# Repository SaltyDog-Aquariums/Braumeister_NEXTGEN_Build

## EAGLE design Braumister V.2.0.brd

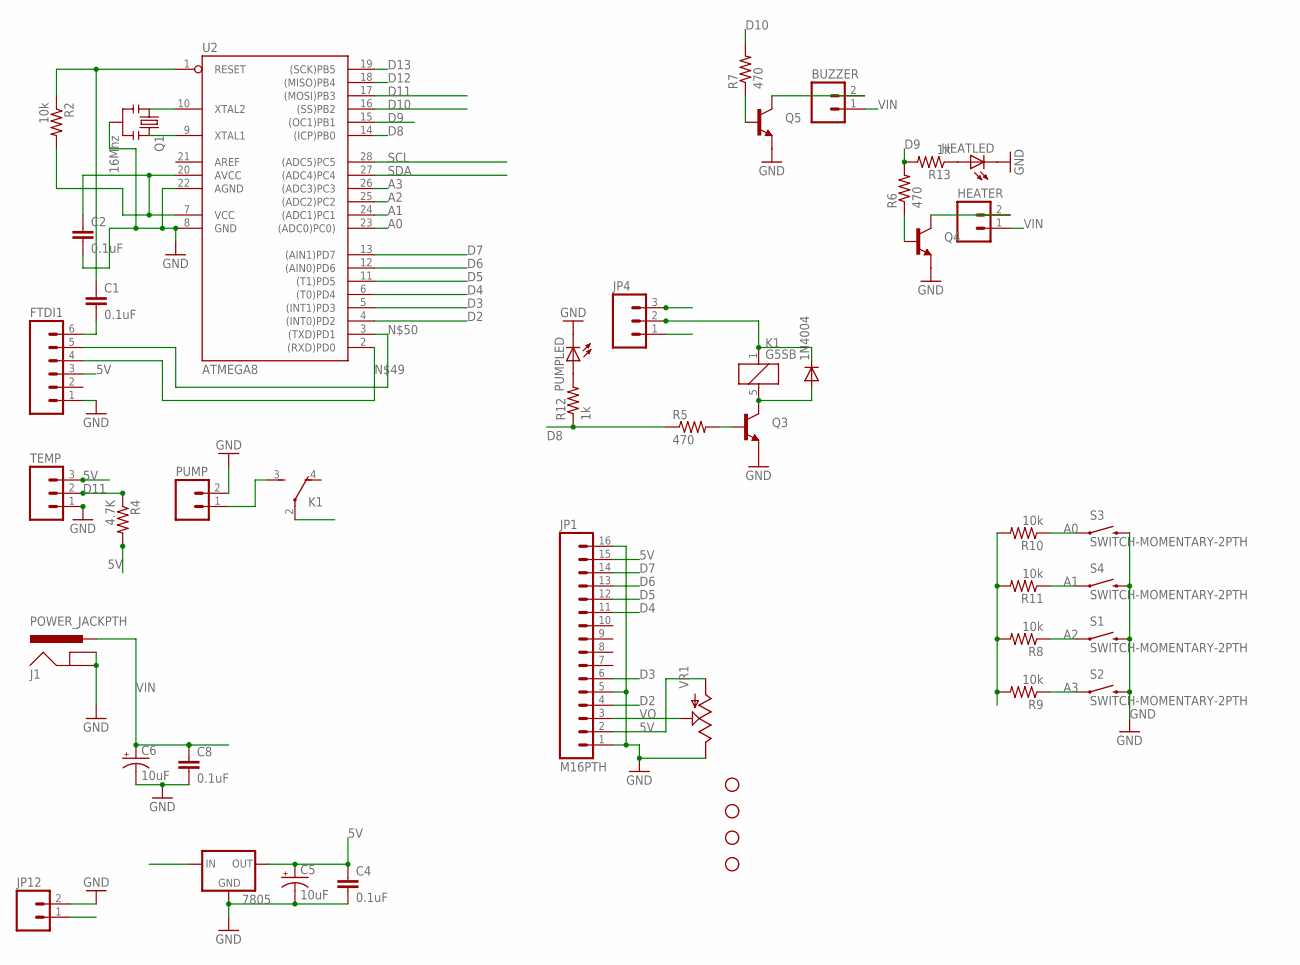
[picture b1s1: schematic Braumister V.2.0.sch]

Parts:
1N4004: DIODEPTH; DIODE-1N4001
7805: V_REG_78XX; TO220AHV
BUZZER: M023.5MM; SCREWTERMINAL-3.5MM-2
C1, C2, C4, C8: 0.1uF; CAP-PTH-SMALL
C5, C6: 10uF; CAP6.3MM2.5MM
FTDI1: M06SIP; 1X06
HEATER: M023.5MM; SCREWTERMINAL-3.5MM-2
HEATLED: LED3MM
J1: POWER_JACKPTH; POWER_JACK_PTH
JP1: M16PTH; 1X16
JP2, JP7, JP9, JP10: STAND-OFF
JP4: M03LOCK; 1X03_LOCK
JP12: M02PTH; 1X02
K1: G5SB
PUMP: M023.5MM; SCREWTERMINAL-3.5MM-2
PUMPLED: LED3MM
Q1: 16Mhz; RESONATOR-PTH
Q3, Q4, Q5: TRANSISTOR_NPNTO-92-AMMO; TO-92-AMMO
R2, R8, R9, R10, R11: 10k; 0204/7
R4: 4.7K; 0204/7
R5, R6, R7: 470; 0204/7
R12, R13: 1k; 0204/7
S1, S2, S3, S4: SWITCH-MOMENTARY-2PTH; TACTILE-PTH
TEMP: M03SCREW; SCREWTERMINAL-3.5MM-3
U2: ATMEGA8; DIL28-3
VR1: POT; TRIM_POT_SIDE

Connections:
5V: 7805.E (OUT), C2.1, C4.1, C5.P$2 (+), FTDI1.3, JP1.2, JP1.15, JP4.3, R2.2, R4.2, R8.2, R9.2, R10.2, R11.2, TEMP.3, U2.7 (VCC), U2.20 (AVCC), VR1.P$3 (A)
A0: R10.1, S3.1, U2.23 ((ADC0)PC0))
A1: R11.1, S4.1, U2.24 ((ADC1)PC1)
A2: R8.1, S1.1, U2.25 ((ADC2)PC2)
A3: R9.1, S2.1, U2.26 ((ADC3)PC3)
D2: JP1.4, U2.4 ((INT0)PD2)
D3: JP1.6, U2.5 ((INT1)PD3)
D4: JP1.11, U2.6 ((T0)PD4)
D5: JP1.12, U2.11 ((T1)PD5)
D6: JP1.13, U2.12 ((AIN0)PD6)
D7: JP1.14, U2.13 ((AIN1)PD7)
D8: R5.1, R12.1, U2.14 ((ICP)PB0)
D9: R6.2, R13.2, U2.15 ((OC1)PB1)
D10: R7.2, U2.16 ((SS)PB2)
D11: R4.1, TEMP.2, U2.17 ((MOSI)PB3)
D12: U2.18 ((MISO)PB4)
D13: U2.19 ((SCK)PB5)
GND: 7805.C (GND), C2.2, C4.2, C5.P$1 (-), C6.P$1 (-), C8.2, FTDI1.1, HEATLED.K (C), J1.GND, J1.GNDBREAK, JP1.1, JP1.5, JP1.16, JP12.2, PUMP.2, PUMPLED.K (C), Q1.2, Q3.1 (E), Q4.1 (E), Q5.1 (E), S1.3 (2), S2.3 (2), S3.3 (2), S4.3 (2), TEMP.1, U2.8 (GND), U2.22 (AGND), VR1.P$1 (E)
unnamed: Q5.2 (B), R7.1
unnamed: K1.3 (S), PUMP.1
unnamed: BUZZER.2, Q5.3 (C)
unnamed: 1N4004.C, JP4.2, K1.1
unnamed: 1N4004.A, K1.5 (2), Q3.3 (C)
unnamed: C1.1, R2.1, U2.1 (RESET)
unnamed: Q3.2 (B), R5.2
unnamed: HEATER.2, Q4.3 (C)
unnamed: Q4.2 (B), R6.1
unnamed: PUMPLED.A, R12.2
unnamed: HEATLED.A, R13.1
unnamed: Q1.3, U2.9 (XTAL1)
unnamed: Q1.1, U2.10 (XTAL2)
unnamed: FTDI1.4, U2.2 ((RXD)PD0)
unnamed: FTDI1.5, U2.3 ((TXD)PD1)
unnamed: C1.2, FTDI1.6
SCL: U2.28 ((ADC5)PC5)
SDA: U2.27 ((ADC4)PC4)
VIN: 7805.B (IN), BUZZER.1, C6.P$2 (+), C8.1, HEATER.1, J1.PWR, JP4.1, JP12.1, K1.2
VO: JP1.3, VR1.P$2 (S)

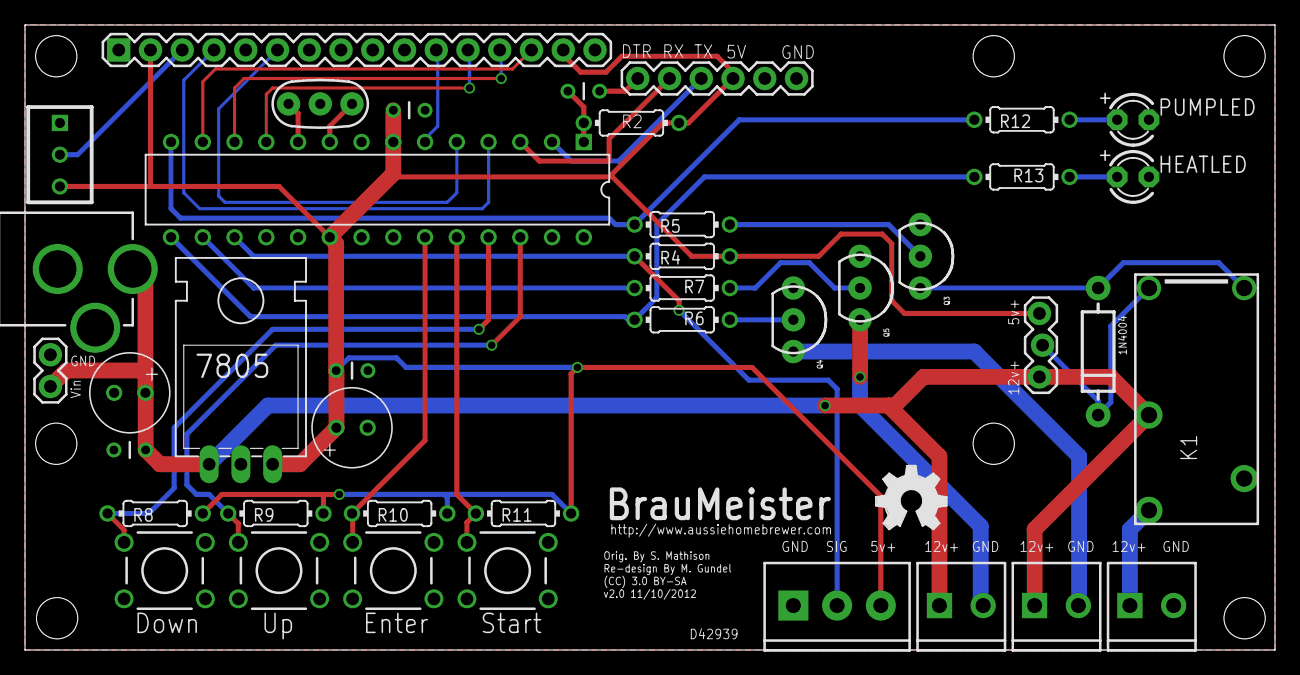
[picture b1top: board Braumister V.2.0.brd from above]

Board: 2 copper layers, 100.0 x 50.0 mm, 49 parts (0 on the bottom side), 34 nets.

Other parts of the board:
JP3, JP5, JP6: STAND-OFF
U$2: OSHW_FILLX200_NOTEXT

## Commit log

2013-04-05 Braumiser
    A DIY approach to the Braumister PID single kettle Brew Controller.
    Topic can be found at
    http://aussiehomebrewer.com/topic/57924-braumeister-nextgen-build/
    Version 1 was designed as a shield by Mathos
    Version 2 was designed as a stand alone controller by M.Gundel aka
    Liquid Arts
